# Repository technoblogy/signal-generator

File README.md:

# Programmable Signal Generator
A digital signal generator capable of generating a square wave from 1kHz to 68MHz. See http://www.technoblogy.com/show?26SM.

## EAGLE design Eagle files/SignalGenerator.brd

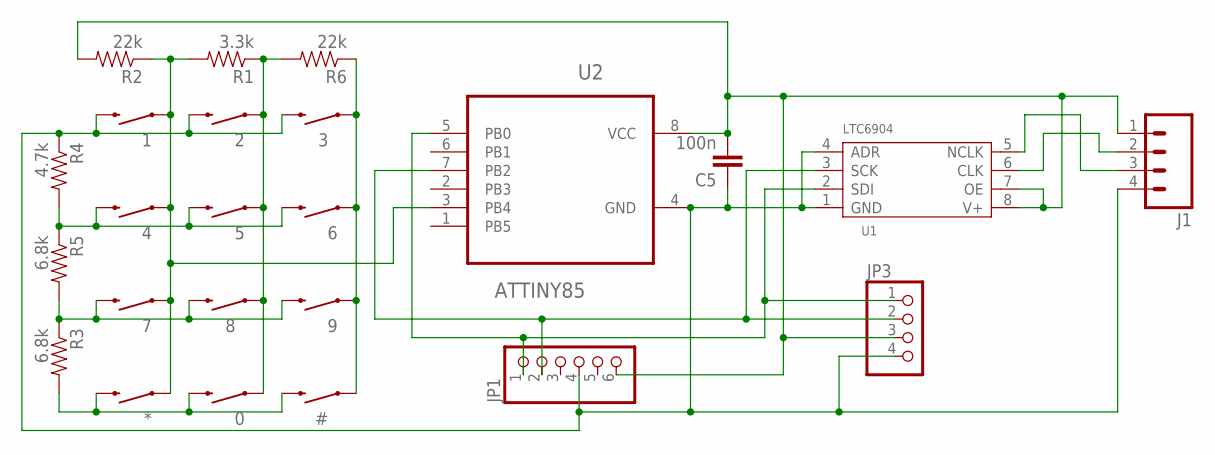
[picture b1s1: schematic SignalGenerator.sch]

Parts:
0, 1, 2, 3, 4, 5, 6, 7, 8, 9: SWITCH-MOMENTARY-2PTH; TACTILE-PTH
#: SWITCH-MOMENTARY-2PTH; TACTILE-PTH
*: SWITCH-MOMENTARY-2PTH; TACTILE-PTH
C5: 100n; 0603-CAP
J1: M04SMD_RA_FEMALE; 1X04_SMD_RA_FEMALE
JP1: HEADER-1X6ROUND; 1X06_ROUND
JP3: HEADER-1X4ROUND; 1X04_ROUND
R1: 3.3k; 0805
R2, R6: 22k; 0805
R3, R5: 6.8k; 0805
R4: 4.7k; 0805
U1: LTC6904; MSOP8-0.65-3X3MM
U2: ATTINY85; SOIC127P798X216-8N

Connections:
GND: 1.3 (2), 2.3 (2), 3.3 (2), C5.1, J1.4, JP1.4, JP3.4, R4.1, U1.1 (GND), U1.4 (ADR), U2.4 (GND)
unnamed: J1.3, U1.5 (NCLK)
unnamed: JP1.2, JP3.2, U1.3 (SCK), U2.7 (PB2)
unnamed: J1.2, U1.6 (CLK)
unnamed: 0.3 (2), #.3 (2), *.3 (2), R3.2
unnamed: 4.3 (2), 5.3 (2), 6.3 (2), R4.2, R5.1
unnamed: 7.3 (2), 8.3 (2), 9.3 (2), R3.1, R5.2
unnamed: 1.1, 4.1, 7.1, *.1, R1.2, R2.1, U2.3 (PB4)
unnamed: JP1.1, JP3.1, U1.2 (SDI), U2.5 (PB0)
unnamed: 0.1, 2.1, 5.1, 8.1, R1.1, R6.2
unnamed: 3.1, 6.1, 9.1, #.1, R6.1
V+: C5.2, J1.1, JP1.6, JP3.3, R2.2, U1.7 (OE), U1.8 (V+), U2.8 (VCC)

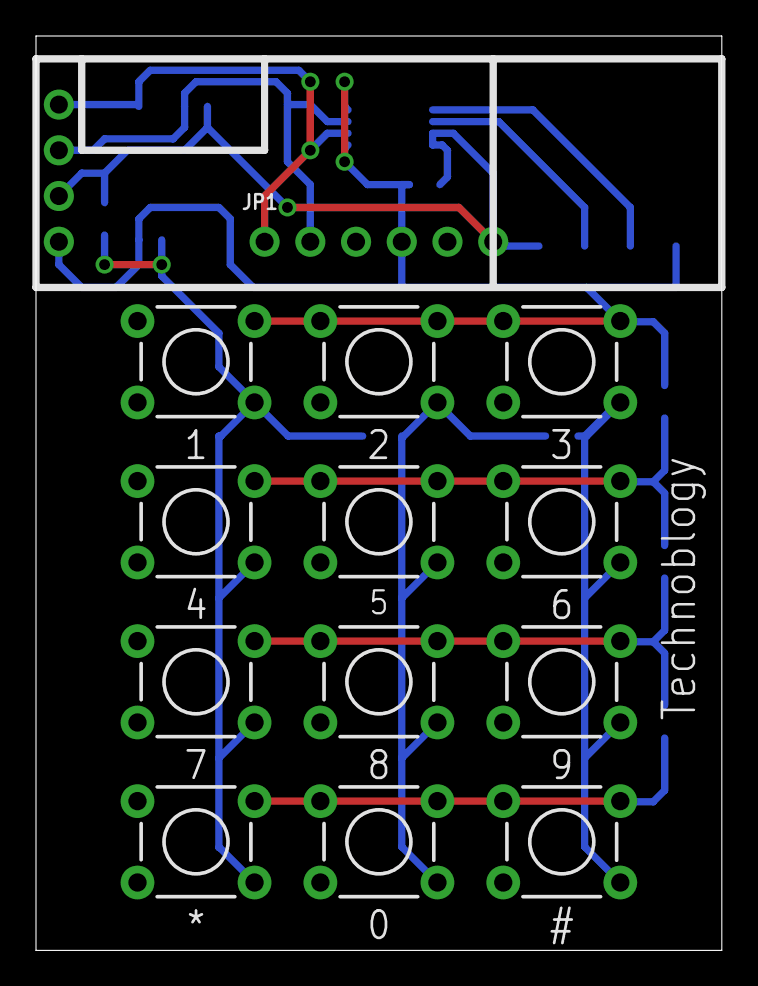
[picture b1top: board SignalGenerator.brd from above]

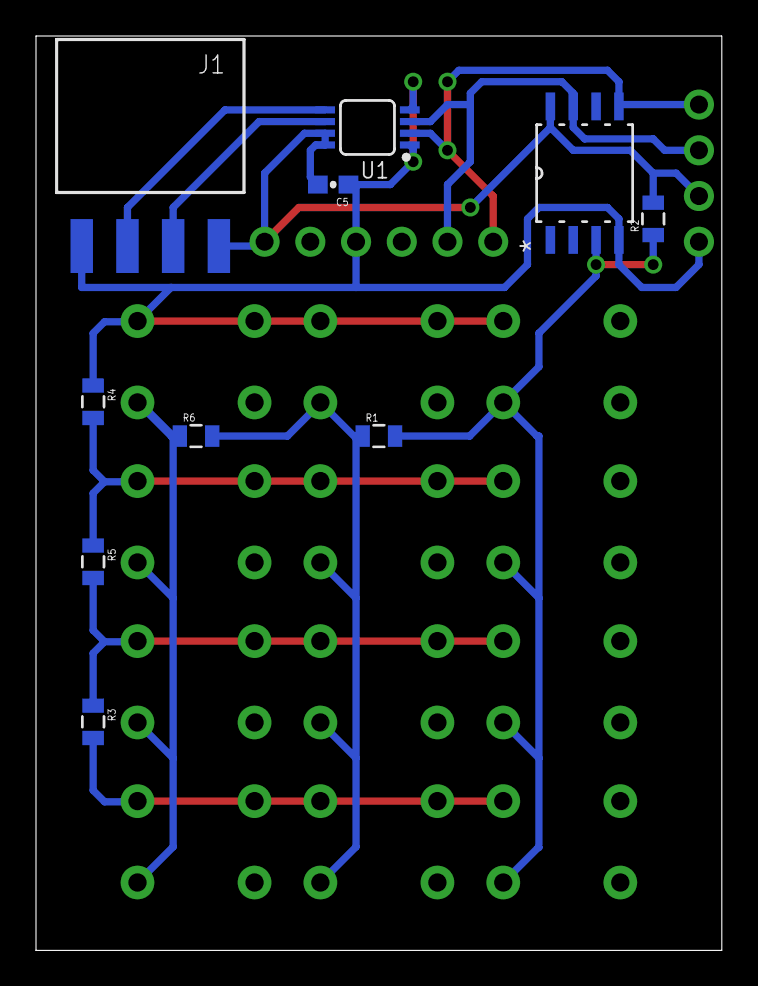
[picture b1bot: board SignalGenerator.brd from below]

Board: 2 copper layers, 38.1 x 50.8 mm, 24 parts (10 on the bottom side), 12 nets.

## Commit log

2018-06-14 Version 1 - 14th June 2018

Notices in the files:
parts and their libraries:
SparkFun-Electromechanical: Licensing: Creative Commons ShareAlike 4.0 International - https://creativecommons.org/licenses/by-sa/4.0
microbuilder: This work is placed in the public domain, and may be freely used for commercial and non-commercial work with the following conditions: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
